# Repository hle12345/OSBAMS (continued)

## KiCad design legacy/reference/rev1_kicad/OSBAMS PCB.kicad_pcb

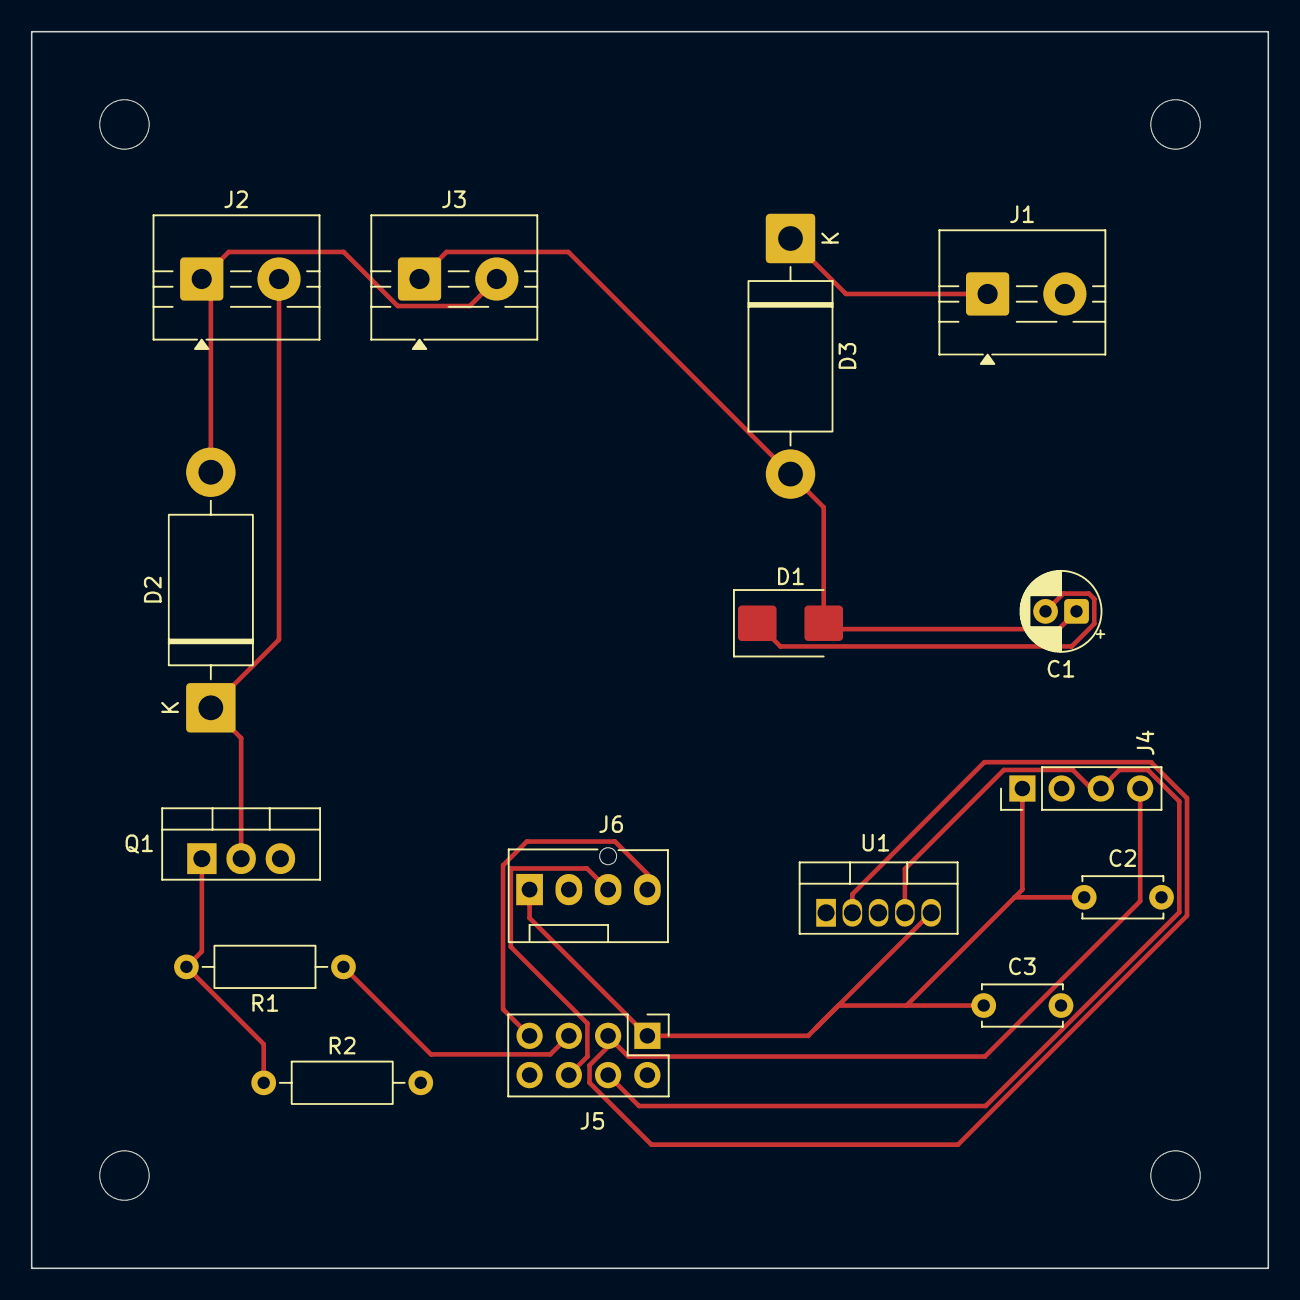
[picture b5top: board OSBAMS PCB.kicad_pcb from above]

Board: 2 copper layers, 80.0 x 80.0 mm, 20 parts (0 on the bottom side), 12 nets.

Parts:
C1: ECA-1EM100I: 10uF 25V (+12V/GND); CP_Radial_D5.0mm_P2.00mm
C2: 0.1uF (TC74 bypass); C_Disc_D5.0mm_W2.5mm_P5.00mm
C3: 0.1uF (logic bypass); C_Disc_D5.0mm_W2.5mm_P5.00mm
D1: SMBJ15A (confirmed, DO-214AA/SMB); D_SMB
D2: 1N5408 (flyback); D_DO-201AD_P15.24mm_Horizontal
D3: SB560-E3/73 (rev-polarity, Schottky); D_DO-201AD_P15.24mm_Horizontal
J1: PWR_IN_12V; TerminalBlock_MaiXu_MX126-5.0-02P_1x02_P5.00mm
J2: CONTACTOR_COIL; TerminalBlock_MaiXu_MX126-5.0-02P_1x02_P5.00mm
J3: ESTOP_LOOP; TerminalBlock_MaiXu_MX126-5.0-02P_1x02_P5.00mm
J4: INA228_MODULE; PinHeader_1x04_P2.54mm_Vertical
J5: NUCLEO_INTERFACE; PinHeader_2x04_P2.54mm_Vertical
J6: UART_HDR; FanPinHeader_1x04_P2.54mm_Vertical
MH1, MH2, MH3, MH4: MountingHole_3.2mm_M3
Q1: IRLZ44NPBF; TO-220-3_Vertical
R1: 220 (gate); R_Axial_DIN0207_L6.3mm_D2.5mm_P10.16mm_Horizontal
R2: 10k (gate pulldown); R_Axial_DIN0207_L6.3mm_D2.5mm_P10.16mm_Horizontal
U1: TC74A5-3.3VAT; TO-220-5_Vertical

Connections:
/12V_IN: D3.1, J1.1
/+3V3: C2.1, C3.1, J4.1, J5.1, J6.1, U1.5 (VDD)
/+12V: C1.1, D1.2, D3.2, J3.1
/COIL_SW: D2.1, J2.2, Q1.2 (D)
/COIL_V: D2.2, J2.1, J3.2
/GATE: Q1.1 (G), R1.2, R2.1
/GND: C1.2, C2.2, C3.2, D1.1, J1.2, J4.2, J5.2, J6.2, Q1.3 (S), R2.2, U1.3 (GND)
/GPIO_GATE: J5.5, R1.1
/SCL: J4.3, J5.4, U1.4 (SCLK)
/SDA: J4.4, J5.3, U1.2 (SDA)
/UART_RX: J5.7, J6.4
/UART_TX: J5.6, J6.3

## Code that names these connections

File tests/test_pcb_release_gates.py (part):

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        self.assertNotIn("+5V", nets)
        self.assertNotIn("5V", nets)
        u1 = D.COMPS["U1"]["nets"]
        for pin, net in (("PA0", "ESTOP_SENSE"), ("PA1", "ADC_SENSE"), ("PC8", "LOAD_EN"), ("PC9", "RELAY_FB"), ("PC10", "ARM_SENSE"), ("PB8", "SCL1"), ("PB9", "SDA1"), ("PB10", "SCL2"), ("PB11", "SDA2"),
                         ("PA2", "UART_TX_MCU"), ("PA3", "UART_RX_MCU")):
            self.assertEqual(u1[pin], net)
        # the MCU reaches the coil only through R21 -> Q1 gate; sensing nets never reach the coil path
        self.assertEqual({r for r, _ in nets["LOAD_EN"]}, {"U1", "R21", "TP26"})
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
    def test_plan_covers_all_mandatory_items_and_is_not_applied(self):
        plan = open(os.path.join(PCB, "REV2_SCHEMATIC_PCB_PLAN.md")).read()
        for kw in ("polarity", "PA0", "PC9", "PA1", "Kelvin", "ARM", "MPN", "test point", "marking"):
            self.assertIn(kw.lower(), plan.lower(), kw)
        for f in ("RELAY_VERIFICATION.md", "PI_POWER_ARCHITECTURE.md", "MANUFACTURING_STATE.md"):
            self.assertTrue(os.path.getsize(os.path.join(PCB, f)) > 0, f)
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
